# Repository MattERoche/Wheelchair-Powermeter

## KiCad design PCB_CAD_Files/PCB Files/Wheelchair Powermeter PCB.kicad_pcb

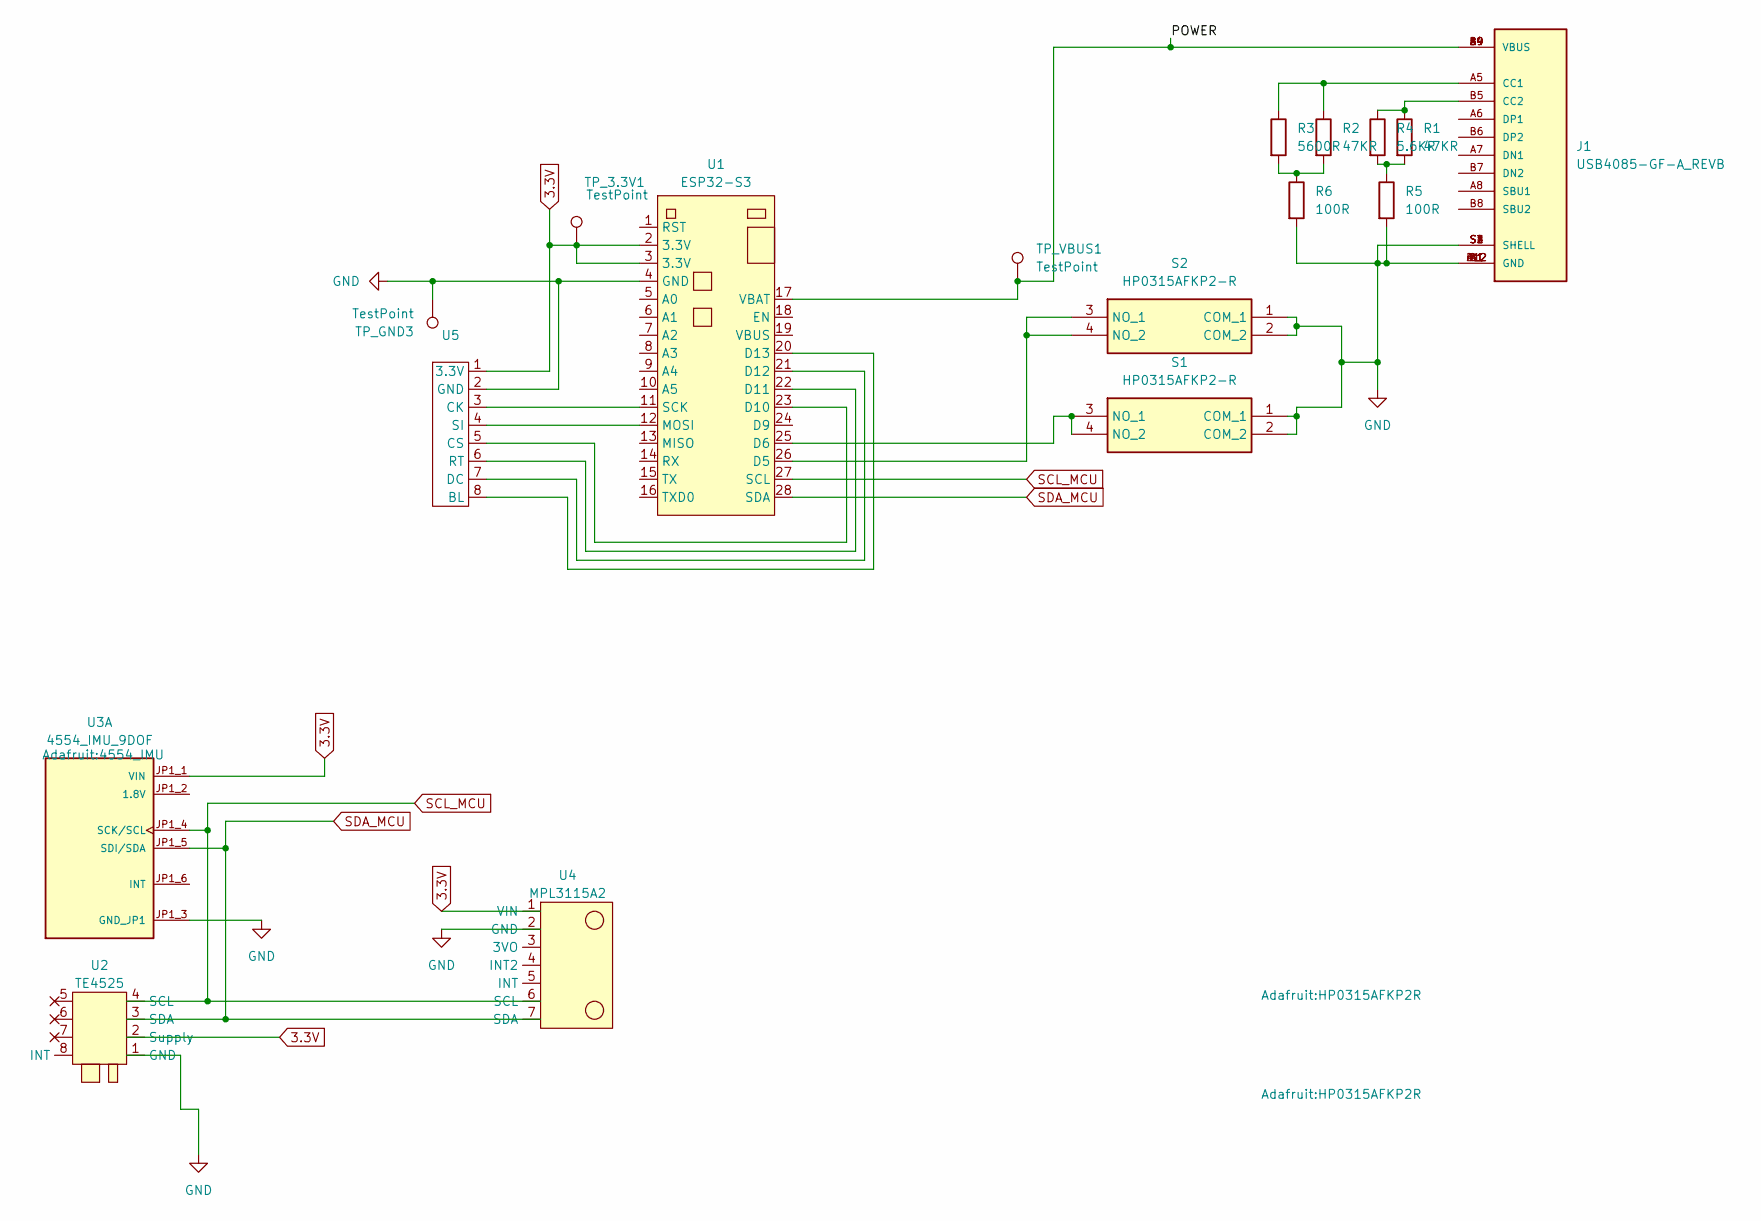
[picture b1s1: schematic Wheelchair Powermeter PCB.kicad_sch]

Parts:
J1: USB4085-GF-A_REVB; GCT_USB4085-GF-A_REVB; PARTREV B
R1, R2: 47KR; R_Axial_DIN0207_L6.3mm_D2.5mm_P7.62mm_Horizontal
R3: 5600R; R_Axial_DIN0207_L6.3mm_D2.5mm_P7.62mm_Horizontal
R4: 5.6KR; R_Axial_DIN0207_L6.3mm_D2.5mm_P7.62mm_Horizontal
R5, R6: 100R; R_Axial_DIN0207_L6.3mm_D2.5mm_P7.62mm_Horizontal
S1, S2: HP0315AFKP2-R; HP0315AFKP2R; Mouser Part Number 633-HP0315AFKP2-R
TP_3.3V1: TestPoint; TestPoint_Loop_D3.80mm_Drill2.5mm
TP_GND3: TestPoint; TestPoint_Loop_D3.80mm_Drill2.5mm
TP_VBUS1: TestPoint; TestPoint_Loop_D3.80mm_Drill2.5mm
U1: ESP32-S3
U2: TE4525; TE_4525-DS5A001DP
U3: 4554_IMU_9DOF; 4554_IMU; PARTREV N/A
U4: MPL3115A2; MPL311
U5: SPI_Screen

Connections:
3.3V: TP_3.3V1.1, U1.2 (3.3V), U1.3 (3.3V), U2.2 (Supply), U3.JP1_1 (VIN), U4.1 (VIN), U5.1 (3.3V)
/POWER: J1.A4 (VBUS), J1.A9 (VBUS), J1.B4 (VBUS), J1.B9 (VBUS), TP_VBUS1.1, U1.17 (VBAT)
GND: J1.A1 (GND), J1.A12 (GND), J1.B1 (GND), J1.B12 (GND), J1.S1 (SHELL), J1.S2 (SHELL), J1.S3 (SHELL), J1.S4 (SHELL), R5.2, R6.2, S1.1 (COM_1), S1.2 (COM_2), S2.1 (COM_1), S2.2 (COM_2), TP_GND3.1, U1.4 (GND), U2.1 (GND), U3.JP1_3 (GND_JP1), U4.2 (GND), U5.2 (GND)
unnamed: J1.A5 (CC1), R2.1, R3.1
unnamed: J1.B5 (CC2), R1.1, R4.1
unnamed: R1.2, R4.2, R5.1
unnamed: R2.2, R3.2, R6.1
unnamed: S1.3 (NO_1), S1.4 (NO_2), U1.25 (D6)
unnamed: S2.3 (NO_1), S2.4 (NO_2), U1.26 (D5)
unnamed: U1.23 (D10), U5.5 (CS)
unnamed: U1.22 (D11), U5.6 (RT)
unnamed: U1.21 (D12), U5.7 (DC)
unnamed: U1.20 (D13), U5.8 (BL)
unnamed: U1.12 (MOSI), U5.4 (SI)
unnamed: U1.11 (SCK), U5.3 (CK)
SCL_MCU: U1.27 (SCL), U2.4 (SCL), U3.JP1_4 (SCK/SCL), U4.6 (SCL)
SDA_MCU: U1.28 (SDA), U2.3 (SDA), U3.JP1_5 (SDI/SDA), U4.7 (SDA)

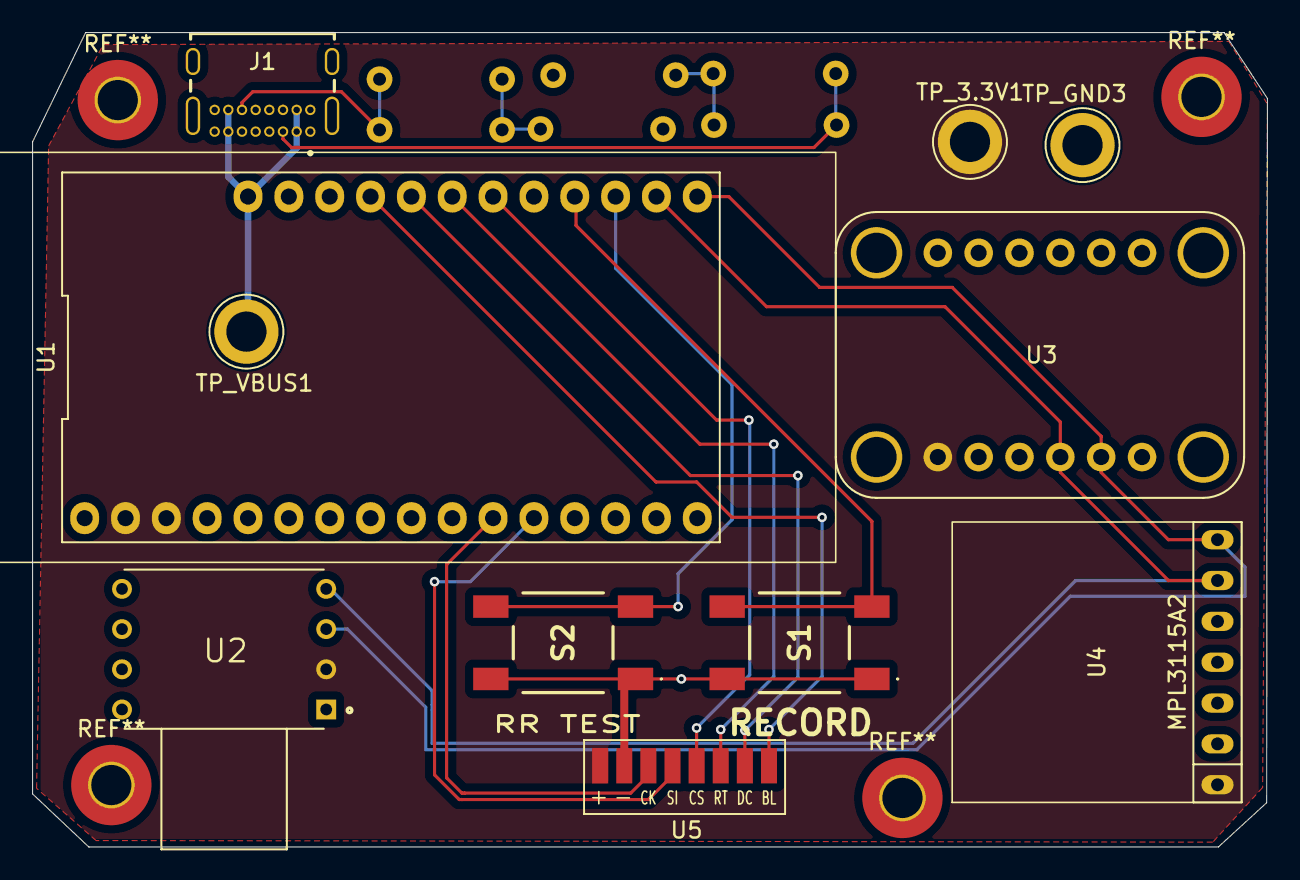
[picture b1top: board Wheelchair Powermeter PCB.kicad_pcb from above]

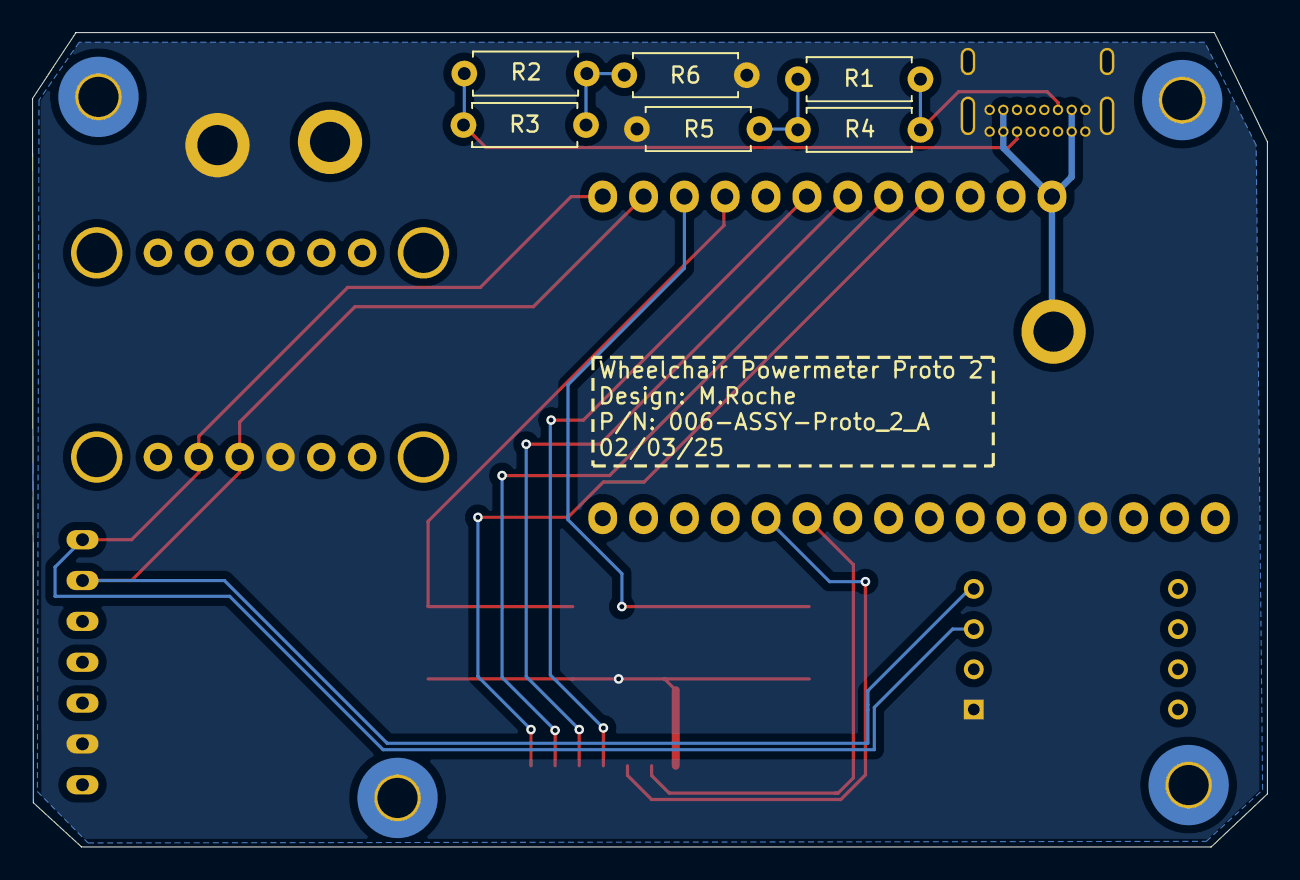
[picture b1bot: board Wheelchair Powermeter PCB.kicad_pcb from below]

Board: 2 copper layers, 76.8 x 50.7 mm, 17 parts (6 on the bottom side), 17 nets.

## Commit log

2025-02-20 Data Commit
2025-02-21 Power Module Commit
2025-02-22 code.py Garbage collect and I2C optimisation
2025-03-03 PCB ADD
2025-03-10 PCB Files
2025-03-24 Big dump
2025-03-31 Moooorrrrrrr
2025-04-02 REorg for sanity and Code Commit
2025-04-07 Penultimate commit pre hand in
2025-04-21 Final Commit to main
